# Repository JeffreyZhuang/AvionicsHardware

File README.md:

# AvionicsHardware

Custom ARM-Cortex M4 STM32F446 flight computer for UAVs

See updated repository for better design

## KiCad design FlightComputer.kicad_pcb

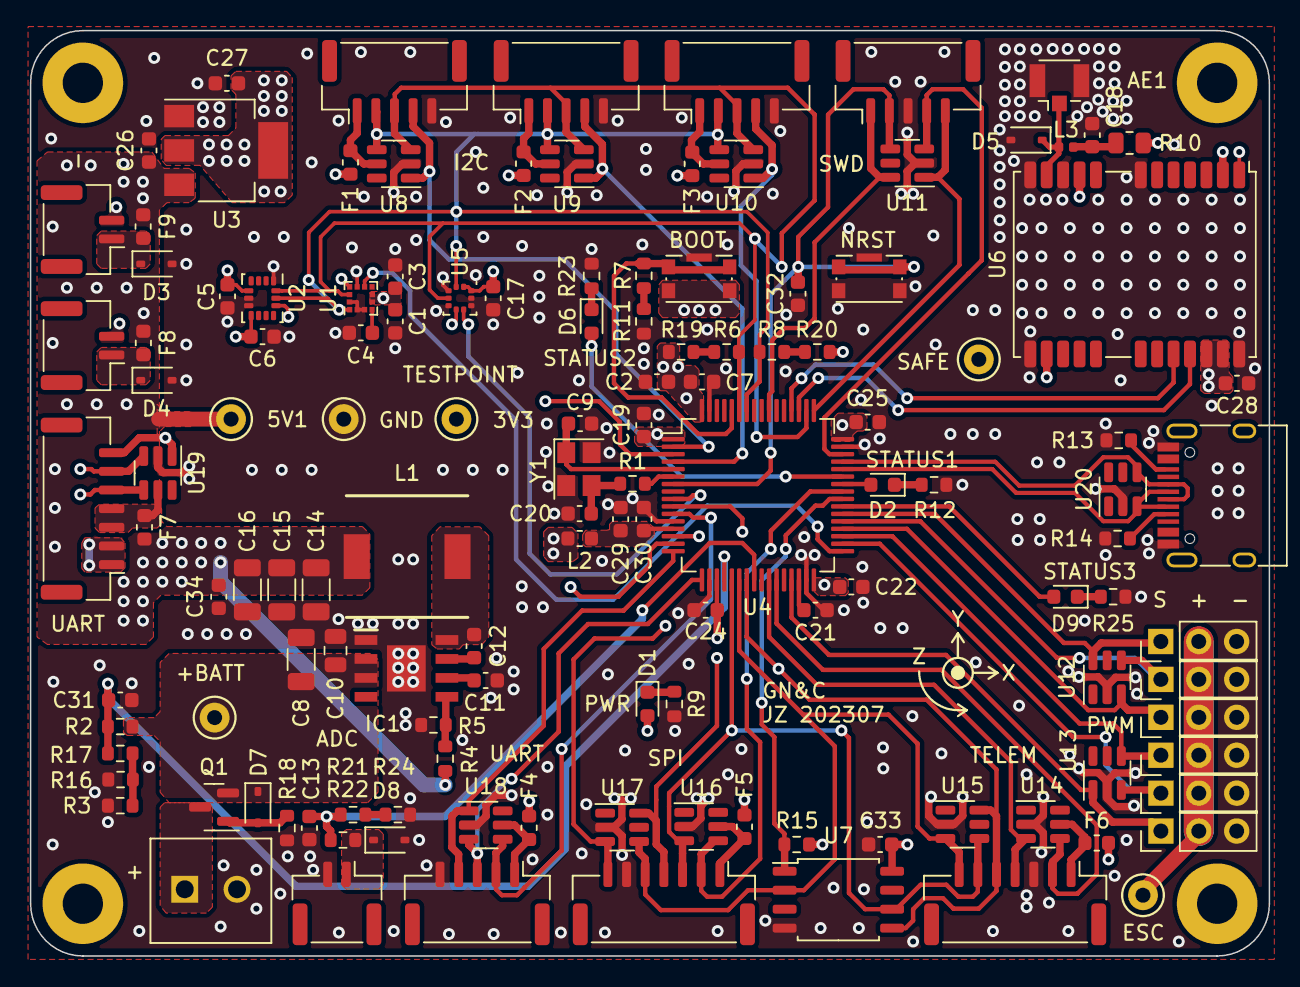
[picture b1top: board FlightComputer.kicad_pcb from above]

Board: 4 copper layers, 83.0 x 62.0 mm, 134 parts (0 on the bottom side), 83 nets.

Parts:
AE1: Antenna; U.FL_Hirose_U.FL-R-SMT-1_Vertical
C1, C11, C28, C29: 1uF; C_0603_1608Metric
C2, C21, C26, C27: 4.7uF; C_0603_1608Metric
C3, C4, C5, C6, C7, C12, C13, C17, C19, C22, C24, C25, C31, C32, C33, C34: 0.1uF; C_0603_1608Metric
C8: 10uF; C_1206_3216Metric
C9, C20: 12pF; C_0603_1608Metric
C10: 220nF; C_0805_2012Metric
C14, C15, C16: 22uF; C_1206_3216Metric
C18: X7R 0.1uF 10% 16V; C_0603_1608Metric
C30: 10nF; C_0603_1608Metric
D1: RED; LED_0603_1608Metric
D2, D6, D9: GREEN; LED_0603_1608Metric
D3, D4, D5, D8: TPESD5V0U1UA; D_SOD-323
D7: PDZ10B,115 10V 400mW; D_SOD-323
F1, F2, F3, F4, F5, F6, F8, F9: 0467.250NRHF 250mAh; Fuse_0603_1608Metric
F7: F0603HI2500V032T 2.5A; Fuse_0603_1608Metric
H1, H2, H3, H4: MountingHole; MountingHole_2.7mm_M2.5_Pad
IC1: LMR33640DDDAR
J1, J4, J6, J8, J9: SM05B-GHS-TB; JST_GH_BM05B-GHS-TBT_1x05-1MP_P1.25mm_Vertical
J2: Screw_Terminal_01x02; OST_OSTTE020104
J3, J5, J7: SM07B-GHS-TB; JST_GH_BM07B-GHS-TBT_1x07-1MP_P1.25mm_Vertical
J10, J11, J12, J14, J15, J16: Header1x3Pin; PinHeader_1x03_P2.54mm_Vertical
J13, J17, J19: SM02B-GHS-TB; JST_GH_BM02B-GHS-TBT_1x02-1MP_P1.25mm_Vertical
J18: USB_C_Receptacle; USB_C_Receptacle_HRO_TYPE-C-31-M-12
L1: 1217AS-H-3R3N 3.3uH 6.8A 14.4mOhm; 1217AS-H-3R3N_P3
L2: 39nH; L_0603_1608Metric
L3: 27nH >300mA >500R @ GNSS Freq.; L_0402_1005Metric
Q1: SI2369BDS-T1-GE3 30V 5.6A; SOT-23
R1: 47R; R_0603_1608Metric
R2, R4, R18: 100k; R_0603_1608Metric
R3, R5, R16, R21, R22, R24: 24.3k; R_0603_1608Metric
R6, R8, R9, R12, R17, R19, R20, R23, R25: 1k; R_0603_1608Metric
R7, R11, R13, R14, R15: 5.1k; R_0603_1608Metric
R10: 10R 10% 0.25W; R_0805_2012Metric
SW1, SW2: KMR221GLFS; SW_Push_1P1T-SH_NO_CK_KMR2xxG
TP1, TP2, TP3, TP4, TP5, TP6: TestPoint; TestPoint_Keystone_5000-5004_Miniature
U1: LIS3MDL; LGA-12_2x2mm_P0.5mm
U2: BMI270; LGA-14_3x2.5mm_P0.5mm_LayoutBorder3x4y
U3: AP7361C-33ER-13; SOT-223-3_TabPin2
U4: STM32F446RET6; LQFP-64_10x10mm_P0.5mm
U5: LPS22HH; ST_HLGA-10_2x2mm_P0.5mm_LayoutBorder3x2y
U6: NEO-M9N; ublox_NEO
U7: W25Q128JVSIQ; SOIC-8_5.23x5.23mm_P1.27mm
U8, U9, U10, U11, U12, U13, U14, U15, U16, U17, U18, U19, U20: USBLC6-4SC6; SOT-23-6
Y1: 16MHz; Crystal_SMD_3225-4Pin_3.2x2.5mm

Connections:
+3V3: C1.1, C2.1, C3.1, C5.1, C6.1, C7.1, C17.1, C19.1, C22.1, C24.1, C25.1, C27.1, C28.1, C33.1, D1.2 (A), F1.2, F2.2, F3.2, F4.2, F5.2, F6.2, L2.1, R15.1, R19.1, R20.1, SW2.2, TP4.1, U1.5 (VDD), U1.6 (VDDIO), U1.10 (CS), U2.5 (VDDIO), U2.8 (VDD), U2.12 (CSB), U3.2 (VO), U4.1 (VBAT), U4.19 (VDD), U4.32 (VDD), U4.48 (VDD), U4.64 (VDD), U5.1 (Vdd_IO), U5.6 (~CS), U5.10 (VDD), U6.2 (D_SEL), U6.14 (LNA_EN), U6.22 (V_BCKP), U6.23 (VCC), U7.8 (VCC)
+5V: C14.1, C15.1, C16.1, C26.1, C34.1, F7.2, F8.1, F9.1, L1.2, R4.1, TP3.1, U3.3 (VI)
+5VA: J10.2, J11.2, J12.2, J14.2, J15.2, J16.2, TP2.1
+BATT: C8.1, C10.1, D7.1 (K), IC1.2 (VIN), IC1.3 (EN), Q1.2 (S), R2.1, TP5.1
ADC12_IN14: C13.1, R21.1, R22.2, U4.24 (PC4)
BOOT0: R7.1, SW2.1, U4.60 (BOOT0)
CE: J3.4, U4.26 (PB0), U14.3 (I/O2)
CSN: J3.2, U4.27 (PB1), U14.4 (I/O3)
CS_EXTRA: J7.2, U4.41 (PA8), U16.4 (I/O3)
ESC: J10.1, U4.38 (PC7), U12.6 (I/O4)
FLASH_CS: R15.2, U4.40 (PC9), U7.1 (~CS)
GND: AE1.2 (Shield), C1.2, C2.2, C3.2, C4.2, C5.2, C6.2, C7.2, C8.2, C9.2, C10.2, C11.2, C13.2, C14.2, C15.2, C16.2, C17.2, C18.2, C19.2, C20.2, C21.2, C22.2, C24.2, C25.2, C26.2, C27.2, C28.2, C29.2, C30.2, C31.2, C32.2, C33.2, C34.2, D3.2 (A), D4.2 (A), D5.2 (A), D8.2 (A), IC1.1 (PGND), IC1.9 (AGND), J1.3, J2.2, J3.3, J4.5, J5.1, J5.2, J6.5, J7.6, J8.5, J9.5, J10.3, J11.3, J12.3, J13.2, J14.3, J15.3, J16.3, J17.2, J18.A1 (GND), J18.A12 (GND), J18.B1 (GND), J18.B12 (GND), J19.2, R3.2, R5.2, R9.2, R11.2, R12.2, R13.2, R14.2, R16.2, R18.2, R23.2, R24.2, R25.2, SW1.2, SW1.SH (GND), SW2.SH (GND), TP1.1, U1.2 (RES), U1.3 (GND), U1.9 (SDO/SA1), U1.12 (RES), U2.1 (SDO), U2.6 (GNDIO), U2.7 (GND), U3.1 (GND), U4.12 (VSSA), U4.18 (VSS), U4.31 (VSS), U4.47 (VSS), U4.63 (VSS), U5.3 (RES), U5.5 (SA0), U5.8 (GND), U5.9 (GND), U6.7 (V_USB), U6.10 (GND), U6.12 (GND), U6.13 (GND), U6.24 (GND), U7.4 (GND), U8.2 (GND), U9.2 (GND), U10.2 (GND), U11.2 (GND), U12.2 (GND), U13.2 (GND), U14.2 (GND), U15.2 (GND), U16.2 (GND), U17.2 (GND), U18.2 (GND), U19.2 (GND), U20.2 (GND), Y1.2, Y1.4
INT1: J4.4, U4.2 (PC13), U8.1 (I/O1)
INT2: J6.4, U4.4 (PC15), U9.1 (I/O1)
INT3: J8.4, U4.50 (PA15), U10.1 (I/O1)
INT4: J9.2, U4.11 (PC3), U18.4 (I/O3)
INT5: J7.7, U4.10 (PC2), U17.3 (I/O2)
INT_BARO: U4.9 (PC1), U5.7 (INT_DRDY)
INT_MAG: U1.8 (DRDY), U4.33 (PB12)
INT_PI: J5.5, U4.3 (PC14), U19.4 (I/O3)
LED1: D2.2 (A), U4.42 (PA9)
LED2: D6.2 (A), U4.43 (PA10)
LED3: D9.2 (A), U4.39 (PC8)
MISO: J3.7, J7.5, U4.22 (PA6), U7.2 (DO(IO1)), U15.3 (I/O2), U17.4 (I/O3)
MOSI: J3.5, J7.4, U4.23 (PA7), U7.5 (DI(IO0)), U15.6 (I/O4), U17.6 (I/O4)
NRST: C32.1, J1.2, SW1.1, U4.7 (NRST), U11.4 (I/O3)
unnamed: AE1.1 (A), D5.1 (K), L3.1, U6.11 (RF_IN)
unnamed: C18.1, L3.2, R10.1
unnamed: C20.1, R1.2, Y1.3
unnamed: D1.1 (K), R9.1
unnamed: D2.1 (K), R12.1
unnamed: D3.1 (K), F9.2, J13.1
unnamed: D4.1 (K), F8.2, J17.1
unnamed: D6.1 (K), R23.1
unnamed: D7.2 (A), Q1.1 (G), R18.1
unnamed: D8.1 (K), J19.1, R22.1
unnamed: D9.1 (K), R25.1
unnamed: C12.1, IC1.7 (BOOT)
unnamed: IC1.5 (FB), R4.2, R5.1
unnamed: C12.2, IC1.8 (SW), L1.1
unnamed: C11.1, IC1.6 (VCC)
unnamed: J2.1, Q1.3 (D)
unnamed: F6.1, J3.1, U14.5 (VBUS)
unnamed: F1.1, J4.1, U8.5 (VBUS)
unnamed: F7.1, J5.3, J5.4, U19.5 (VBUS)
unnamed: F2.1, J6.1, U9.5 (VBUS)
unnamed: F5.1, J7.1, U16.5 (VBUS)
unnamed: F3.1, J8.1, U10.5 (VBUS)
unnamed: F4.1, J9.1, U18.5 (VBUS)
unnamed: J18.A5 (CC1), R14.1
unnamed: J18.B5 (CC2), R13.1
unnamed: R7.2, R11.1
unnamed: R3.1, R16.1, R17.2
unnamed: R6.1, R19.2
unnamed: R8.1, R20.2
unnamed: R21.2, R24.1
unnamed: C4.1, U1.4 (C1)
unnamed: C9.1, U4.5 (PH0), Y1.1
unnamed: R1.1, U4.6 (PH1)
unnamed: C21.1, U4.30 (VCAP_1)
unnamed: C29.1, C30.1, L2.2, U4.13 (VDDA)
unnamed: TP6.1, U6.1 (SAFEBOOT_N)
unnamed: R10.2, U6.9 (VCC_RF)
SCK: J3.6, J7.3, U4.21 (PA5), U7.6 (CLK), U15.4 (I/O3), U16.3 (I/O2)
SCL: J4.2, J6.2, J8.2, R8.2, U1.1 (SCL/SPC), U2.13 (SCX), U4.58 (PB6), U5.2 (SCL), U8.4 (I/O3), U9.4 (I/O3), U10.4 (I/O3)
SDA: J4.3, J6.3, J8.3, R6.2, U1.11 (SDA), U2.14 (SDX), U4.59 (PB7), U5.4 (SDA), U8.3 (I/O2), U9.3 (I/O2), U10.3 (I/O2)
SWCLK: J1.5, U4.49 (PA14), U11.1 (I/O1)
SWDIO: J1.4, U4.46 (PA13), U11.3 (I/O2)
SWO: J1.1, U4.55 (PB3), U11.6 (I/O4)
Servo 1: J11.1, U4.29 (PB10), U13.1 (I/O1)
Servo 2: J12.1, U4.34 (PB13), U13.3 (I/O2)
Servo 3: J14.1, U4.35 (PB14), U13.4 (I/O3)
Servo 4: J15.1, U4.36 (PB15), U12.3 (I/O2)
Servo 5: J16.1, U4.37 (PC6), U12.4 (I/O3)
UART4_RX: J5.6, U4.15 (PA1), U19.3 (I/O2)
UART4_TX: J5.7, U4.14 (PA0), U19.1 (I/O1)
USART2_RX: J9.3, U4.17 (PA3), U18.3 (I/O2)
USART2_TX: J9.4, U4.16 (PA2), U18.1 (I/O1)
USART3_RX: U4.52 (PC11), U6.20 (TXD/SPI_MISO)
USART3_TX: U4.51 (PC10), U6.21 (RXD/SPI_MOSI)
USB_D+: J18.A6 (D+), J18.B6 (D+), U4.45 (PA12), U20.4 (I/O3)
USB_D-: J18.A7 (D-), J18.B7 (D-), U4.44 (PA11), U20.3 (I/O2)
V_BAT_SENSE: C31.1, R2.2, R17.1, U4.20 (PA4)

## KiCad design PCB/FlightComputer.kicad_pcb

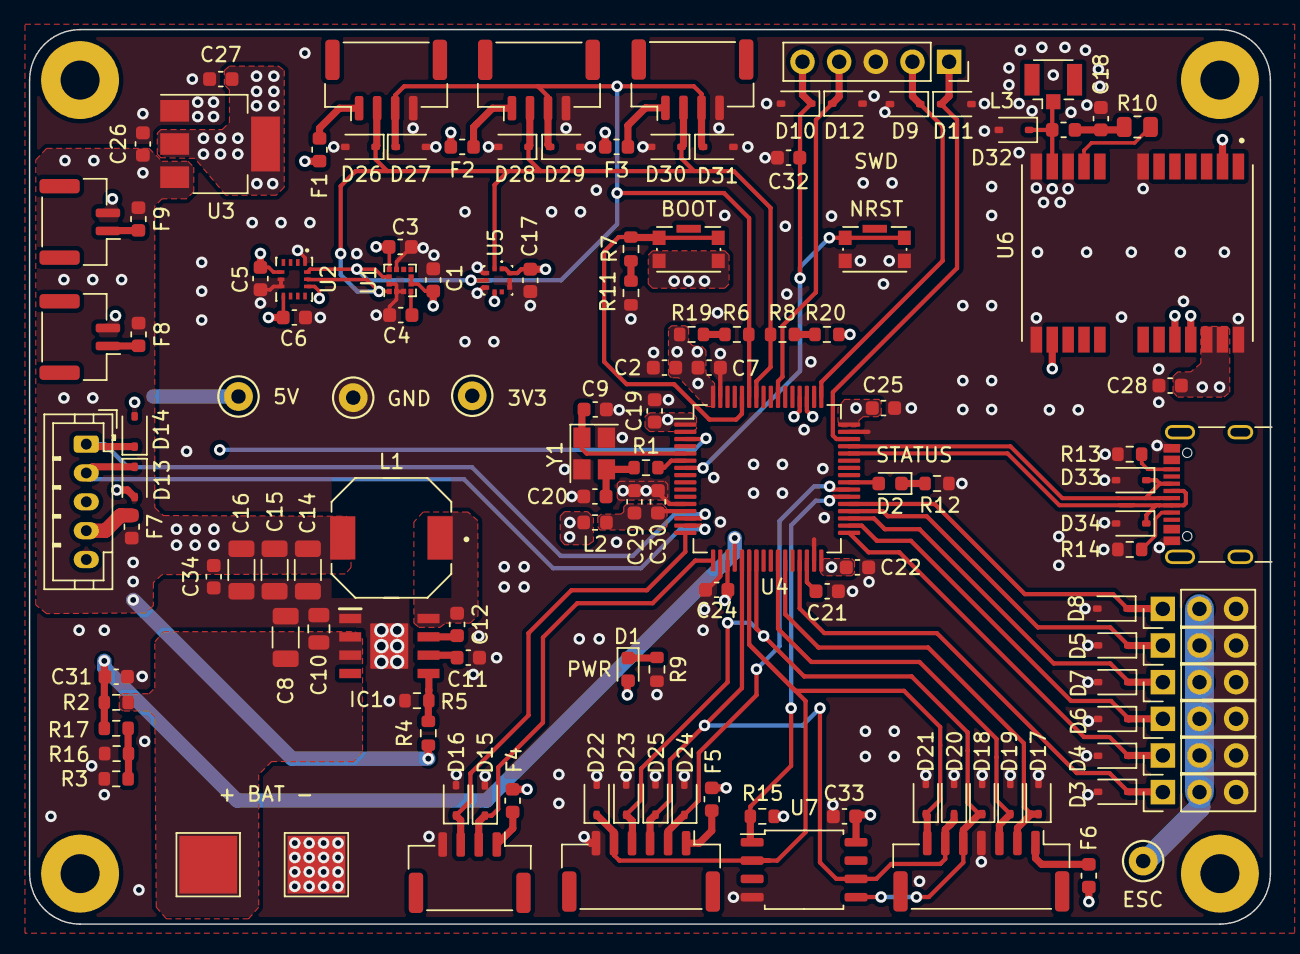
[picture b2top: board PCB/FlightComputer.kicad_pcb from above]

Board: 4 copper layers, 86.0 x 62.0 mm, 136 parts (0 on the bottom side), 66 nets.

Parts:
AE1: Antenna; U.FL_Hirose_U.FL-R-SMT-1_Vertical
C1, C11, C28, C29: 1uF; C_0603_1608Metric
C2, C21, C26, C27: 4.7uF; C_0603_1608Metric
C3, C4, C5, C6, C7, C12, C17, C19, C22, C24, C25, C31, C32, C33, C34: 0.1uF; C_0603_1608Metric
C8: 10uF; C_1206_3216Metric
C9, C20: 12pF; C_0603_1608Metric
C10: 220nF; C_0805_2012Metric
C14, C15, C16: 22uF; C_1206_3216Metric
C18: X7R 0.1uF 10% 16V; C_0603_1608Metric
C30: 10nF; C_0603_1608Metric
D1: RED; LED_0603_1608Metric
D2: GREEN; LED_0603_1608Metric
D3, D4, D5, D6, D7, D8, D9, D10, D11, D12, D13, D14, D15, D16, D17, D18, D19, D20, D21, D22, D23, D24, D25, D26, D27, D28, D29, D30, D31, D32, D33, D34: D; D_SOD-323
F1, F2, F3, F4, F5, F6, F8, F9: 0467.250NRHF 250mAh; Fuse_0603_1608Metric
F7: ERB-RE2R50V 2.5A; Fuse_0603_1608Metric
H1, H2, H3, H4: MountingHole; MountingHole_2.7mm_M2.5_Pad
IC1: LMR33640DDDAR; SOIC127P600X170-9N
J1: Conn_01x05; PinSocket_1x05_P2.54mm_Vertical
J2, J13: Conn_01x02; JST_GH_BM02B-GHS-TBT_1x02-1MP_P1.25mm_Vertical
J3: Conn_01x07; JST_GH_BM07B-GHS-TBT_1x07-1MP_P1.25mm_Vertical
J4, J6, J8, J9: Conn_01x04; JST_GH_BM04B-GHS-TBT_1x04-1MP_P1.25mm_Vertical
J5: Conn_01x04; JST_PH_B5B-PH-K_1x05_P2.00mm_Vertical
J7: Conn_01x06; JST_GH_BM06B-GHS-TBT_1x06-1MP_P1.25mm_Vertical
J10, J11, J12, J14, J15, J16: Header1x3Pin; PinHeader_1x03_P2.54mm_Vertical
J17, J19: Conn_01x01; TestPoint_Pad_4.0x4.0mm
J18: USB_C_Receptacle; USB_C_Receptacle_GCT_USB4105-xx-A_16P_TopMnt_Horizontal
L1: 1217AS-H-3R3N 3.3uH 6.8A 14.4mOhm; IND_1217AS-H-3R3N=P3
L2: 39nH; L_0603_1608Metric
L3: 27nH >300mA >500ohm; L_0603_1608Metric
R1: 47ohm; R_0603_1608Metric
R2, R4: 100k; R_0603_1608Metric
R3, R5, R16: 24.3k; R_0603_1608Metric
R6, R8, R9, R12, R15, R17, R19, R20: 1k; R_0603_1608Metric
R7, R11, R13, R14: 5.1k; R_0603_1608Metric
R10: 10ohm 10% 0.25W; R_0805_2012Metric
SW1, SW2: KMR221GLFS; SW_Push_1P1T-SH_NO_CK_KMR2xxG
TP1, TP2, TP3, TP4: TestPoint; TestPoint_Keystone_5000-5004_Miniature
U1: LIS3MDL; LGA-12_2x2mm_P0.5mm
U2: BMI270; XDCR_BMI270
U3: AP7361C-33ER-13; SOT-223-3_TabPin2
U4: STM32F446RETx; LQFP-64_10x10mm_P0.5mm
U5: LPS22HH; LPS22HHTR
U6: NEO-M9N; XCVR_NEO-M9N
U7: W25Q128JVS; SOIC-8_5.23x5.23mm_P1.27mm
Y1: 16MHz; Crystal_SMD_3225-4Pin_3.2x2.5mm

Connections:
+3V3: C1.1, C2.1, C3.1, C5.1, C6.1, C7.1, C17.1, C19.1, C22.1, C24.1, C25.1, C27.1, C28.1, C33.1, D1.2 (A), F1.2, F2.2, F3.2, F4.2, F5.2, F6.2, L2.1, R15.1, R19.1, R20.1, SW2.2, TP4.1, U1.5 (VDD), U1.6 (VDDIO), U1.10 (CS), U2.5 (VDDIO), U2.8 (VDD), U2.12 (CSB), U3.2 (VO), U4.1 (VBAT), U4.19 (VDD), U4.32 (VDD), U4.48 (VDD), U4.64 (VDD), U5.1 (Vdd_IO), U5.6 (~CS), U5.10 (VDD), U6.2 (D_SEL), U6.14 (LNA_EN), U6.22 (V_BCKP), U6.23 (VCC), U7.8 (VCC)
+5V: C14.1, C15.1, C16.1, C26.1, C34.1, F7.2, F8.1, F9.1, L1.2, R4.1, TP3.1, U3.3 (VI)
+5VA: J10.2, J11.2, J12.2, J14.2, J15.2, J16.2, TP2.1
+BATT: C8.1, C10.1, IC1.2 (VIN), IC1.3 (EN), J17.1, R2.1
BOOT0: R7.1, SW2.1, U4.60 (BOOT0)
CE: D19.1 (K), J3.3, U4.26 (PB0)
CSN: D17.1 (K), J3.2, U4.27 (PB1)
CS_EXTRA: D24.1 (K), J7.2, U4.39 (PC8)
ESC: D8.1 (K), J10.1, U4.37 (PC6)
FLASH_CS: R15.2, U4.38 (PC7), U7.1 (~CS)
GND: C1.2, C2.2, C3.2, C4.2, C5.2, C6.2, C7.2, C8.2, C9.2, C10.2, C11.2, C14.2, C15.2, C16.2, C17.2, C18.2, C19.2, C20.2, C21.2, C22.2, C24.2, C25.2, C26.2, C27.2, C28.2, C29.2, C30.2, C31.2, C32.2, C33.2, C34.2, D3.2 (A), D4.2 (A), D5.2 (A), D6.2 (A), D7.2 (A), D8.2 (A), D9.2 (A), D10.2 (A), D11.2 (A), D12.2 (A), D13.2 (A), D14.2 (A), D15.2 (A), D16.2 (A), D17.2 (A), D18.2 (A), D19.2 (A), D20.2 (A), D21.2 (A), D22.2 (A), D23.2 (A), D24.2 (A), D25.2 (A), D26.2 (A), D27.2 (A), D28.2 (A), D29.2 (A), D30.2 (A), D31.2 (A), D32.2 (A), D33.2 (A), D34.2 (A), IC1.1 (PGND), IC1.9 (AGND), J1.3, J2.2, J3.4, J4.4, J5.5, J6.4, J7.6, J8.4, J9.4, J10.3, J11.3, J12.3, J13.2, J14.3, J15.3, J16.3, J18.A1 (GND), J18.A12 (GND), J18.B1 (GND), J18.B12 (GND), J19.1, R3.2, R5.2, R9.2, R11.2, R12.1, R13.2, R14.2, R16.2, SW1.2, TP1.1, U1.2 (RES), U1.3 (GND), U1.9 (SDO/SA1), U1.12 (RES), U2.1 (SDO), U2.6 (GNDIO), U2.7 (GND), U3.1 (GND), U4.12 (VSSA), U4.18 (VSS), U4.31 (VSS), U4.47 (VSS), U4.63 (VSS), U5.3 (RES), U5.5 (SA0), U5.8 (GND), U5.9 (GND), U6.7 (V_USB), U6.10 (GND), U6.12 (GND), U6.13 (GND), U6.24 (GND), U7.4 (GND), Y1.2, Y1.4
INT_PI: J5.3, U4.3 (PC14)
LED_STATUS: D2.2 (A), U4.40 (PC9)
MISO: D21.1 (K), D22.1 (K), J3.7, J7.5, U4.22 (PA6), U7.2 (DO(IO1))
MOSI: D18.1 (K), D23.1 (K), J3.5, J7.4, U4.23 (PA7), U7.5 (DI(IO0))
NRST: C32.1, D10.1 (K), J1.5, SW1.1, U4.7 (NRST)
unnamed: AE1.1 (A), D32.1 (K), L3.1, U6.11 (RF_IN)
unnamed: C18.1, L3.2, R10.1
unnamed: C20.1, R1.2, Y1.3
unnamed: D1.1 (K), R9.1
unnamed: D2.1 (K), R12.2
unnamed: C12.1, IC1.7 (BOOT)
unnamed: IC1.5 (FB), R4.2, R5.1
unnamed: C12.2, IC1.8 (SW), L1.1
unnamed: C11.1, IC1.6 (VCC)
unnamed: F9.2, J2.1
unnamed: F6.1, J3.1
unnamed: F1.1, J4.1
unnamed: F7.1, J5.4
unnamed: F2.1, J6.1
unnamed: F5.1, J7.1
unnamed: F3.1, J8.1
unnamed: F4.1, J9.1
unnamed: F8.2, J13.1
unnamed: J18.A5 (CC1), R14.1
unnamed: J18.B5 (CC2), R13.1
unnamed: R7.2, R11.1
unnamed: R3.1, R16.1, R17.2
unnamed: R6.1, R19.2
unnamed: R8.1, R20.2
unnamed: C4.1, U1.4 (C1)
unnamed: C9.1, U4.5 (PH0), Y1.1
unnamed: R1.1, U4.6 (PH1)
unnamed: C21.1, U4.30 (VCAP_1)
unnamed: C29.1, C30.1, L2.2, U4.13 (VDDA)
unnamed: R10.2, U6.9 (VCC_RF)
SCK: D20.1 (K), D25.1 (K), J3.6, J7.3, U4.21 (PA5), U7.6 (CLK)
SCL: D26.1 (K), D28.1 (K), D30.1 (K), J4.2, J6.2, J8.2, R8.2, U1.1 (SCL/SPC), U2.13 (SCX), U4.58 (PB6), U5.2 (SCL)
SDA: D27.1 (K), D29.1 (K), D31.1 (K), J4.3, J6.3, J8.3, R6.2, U1.11 (SDA), U2.14 (SDX), U4.59 (PB7), U5.4 (SDA)
SWCLK: D9.1 (K), J1.2, U4.49 (PA14)
SWDIO: D11.1 (K), J1.1, U4.46 (PA13)
SWO: D12.1 (K), J1.4, U4.55 (PB3)
Servo 1: D3.1 (K), J11.1, U4.29 (PB10)
Servo 2: D4.1 (K), J12.1, U4.33 (PB12)
Servo 3: D6.1 (K), J14.1, U4.34 (PB13)
Servo 4: D7.1 (K), J15.1, U4.35 (PB14)
Servo 5: D5.1 (K), J16.1, U4.36 (PB15)
UART4_RX: D13.1 (K), J5.2, U4.15 (PA1)
UART4_TX: D14.1 (K), J5.1, U4.14 (PA0)
USART2_RX: D15.1 (K), J9.2, U4.17 (PA3)
USART2_TX: D16.1 (K), J9.3, U4.16 (PA2)
USART3_RX: U4.52 (PC11), U6.20 (TXD/SPI_MISO)
USART3_TX: U4.51 (PC10), U6.21 (RXD/SPI_MOSI)
USB_D+: D33.1 (K), J18.A6 (D+), J18.B6 (D+), U4.45 (PA12)
USB_D-: D34.1 (K), J18.A7 (D-), J18.B7 (D-), U4.44 (PA11)
V_BAT_SENSE: C31.1, R2.2, R17.1, U4.20 (PA4)

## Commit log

2023-06-21 Create PCB
2023-06-21 Create askjdhsda
2023-06-21 Create aksdjsahd
2023-07-08 Create askdjashdsa
2023-07-08 Create kdjsah
2023-07-10 Create jhfdsf
